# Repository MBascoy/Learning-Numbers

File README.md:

# Learning Numbers
This is a little educational game for kids (around 3-5 years old) to learn numbers and counting.

## How to play
The game has 3 modes:
- Easy Mode
- Hard Mode
- Practice Mode

In **Easy Mode** the game displays a random number between 1 and 5, you have to use the two button rows on the bottom to turn on the lights to match the number diplayed (eg: if a 3 is shown you have to press 3 buttons to turn on 3 lights), after that you press "**OK**", if the result is correct you will see a "happy face" and a new number will be shown, if the result is incorrect you will see a "sad face" and you have to correct your answer and try it again.

**Hard Mode** is the same as easy but with numbers between 6 and 16.

In **Practice Mode** the game just show how many lights are on, so you can see which number relates to how many lights are on, (eg: if you turn on 2 lights the display will show you a 2), if you press "**OK**" the game will play an audio of the number that is displayed in the screen.

## How to build
You have to do 3 things:
- Make the 3D design
- Make the PCB (And solder all the components)
- Flash a microcontroller with the code

The components list is the following:

(All the components can be found in Aliexpress)

- 2x matrix led 8x8
- 1x Atmega168pa
- 5x 74HC595 chips
- 2x 74HC165 chips
- 16x 5mm Leds
- 1x 8Mhz crystal oscillator
- 33x 1K resistors
- 16x 10K resistors
- 1x 1Ohm resistor
- 2x 22pf smd capacitors
- 1x 100nf smd capacitor
- 1x 470uf electrolitic capacitor
- 17x SMD Push buttons 12mm
- 5x SMD Push buttons 6mm
- 1x ZIF socket 28pin narrow
- 1x Power switch
- 3x JST connector ph2.0
- 1x battery holder 4x AAA
- 2x Screw M2 inserts (3mm height, 3mm OD)
- 4x M2 Screws
- 2x M2 Nuts
- 6x Screw M3 inserts (5mm height, 5mm OD)
- 4x Screw M3 inserts (3mm height, 5mm OD)
- 8x M3 Screws
- 1x DFPlayer mini
- 1x Speaker 3W 4Ohm PH2.0 terminal

For the **speaker** you need this specific model:

For the **power switch** you need this specific model:

You need to add a JST connector (PH 2.0) to the power switch and the battery holder, this is an image of the power switch with the PH 2.0 connector:

### Make the 3D design
Inside **3D design** folder you can find the 3 .stl files ready to print.

If you want to change the text (currently are on spanish), you can do it inside **global_constants.scad** file, after that you have to re-render **learning_numbers.scad** file with **openSCAD** and export the .stl file.

Once you have the 3D design printed you have to put the **screw inserts**:
- 4x M3 inserts (5mm height, 5mm OD) for the lit

- 2x M3 inserts (5mm height, 5mm OD) for battery lit

- 4x M3 inserts (3mm height, 5mm OD) for the PCB

- 2x M2 inserts (3mm height, 3mm OD) for the speaker

### Make the PCB
Inside **circuit/Learning_Numbers** folder you can find **Gerber.zip** file which has the PCB ready to be created using a your favorite provider. I've use [jlcpcb.com](https://jlcpcb.com).

When you have the PCB you need to solder the components.

Images of the PCB with no components:

Image of the final result with all the components:

### Flash code to microcontroller
The code is ready to flash with a **usbasp** programmer and an **ATMEGA168pa** microcontroller, you only have to go to the **code** folder and run `make flash` command, if you want to use other programmer or microcontroller (an ATMEGA328p for example) you have to update the **Makefile**.

**NOTE:** you have to enable the fuse to use the external crystal, use the following command (for usbasp programmer and atmega168pa microcontroller):
`avrdude -c usbasp -p m168pa -U lfuse:w:0x7F:m`

Once you have flashed the microcontroller just put it inside the ZIF socket on the PCB.

## Audio files
The game uses a **DFPlayer mini** module to play sounds, you need an micro-SD card to put inside the module, the micro-SD card must be formated with **FAT32** file system.

The files inside the micro-SD card must be the followings:

| File name  | Sound         |
| ---------- | ------------- |
| 001.mp3    | Zero          |
| 002.mp3    | One           |
| 003.mp3    | Two           |
| 004.mp3    | Three         |
| 005.mp3    | Four          |
| 006.mp3    | Five          |
| 007.mp3    | Six           |
| 008.mp3    | Seven         |
| 009.mp3    | Eight         |
| 010.mp3    | Nine          |
| 011.mp3    | Ten           |
| 012.mp3    | Eleven        |
| 013.mp3    | Twelve        |
| 014.mp3    | Thriteen      |
| 015.mp3    | Fourteen      |
| 016.mp3    | Fifteen       |
| 017.mp3    | Sixteen       |
| 018.mp3    | Title sound   |
| 019.mp3    | Easy mode     |
| 020.mp3    | Hard mode     |
| 021.mp3    | Practice mode |
| 022.mp3    | Success sound |
| 023.mp3    | Fail sound    |
| 024.mp3    | Volume Up     |
| 025.mp3    | Volume Down   |

You can find sample sounds inside the **audio samples** folder.

If you want to add your custom audios the mp3 files should have this parameters (it's not critical, but better for a good performance):

| Parameters | Value     |
| ---------- | --------- |
| Format     | mp3       |
| Channels   | Mono      |
| Samples    | 44100Hz   |
| Speed mode | Constant  |
| Quality    | 112kbps   |

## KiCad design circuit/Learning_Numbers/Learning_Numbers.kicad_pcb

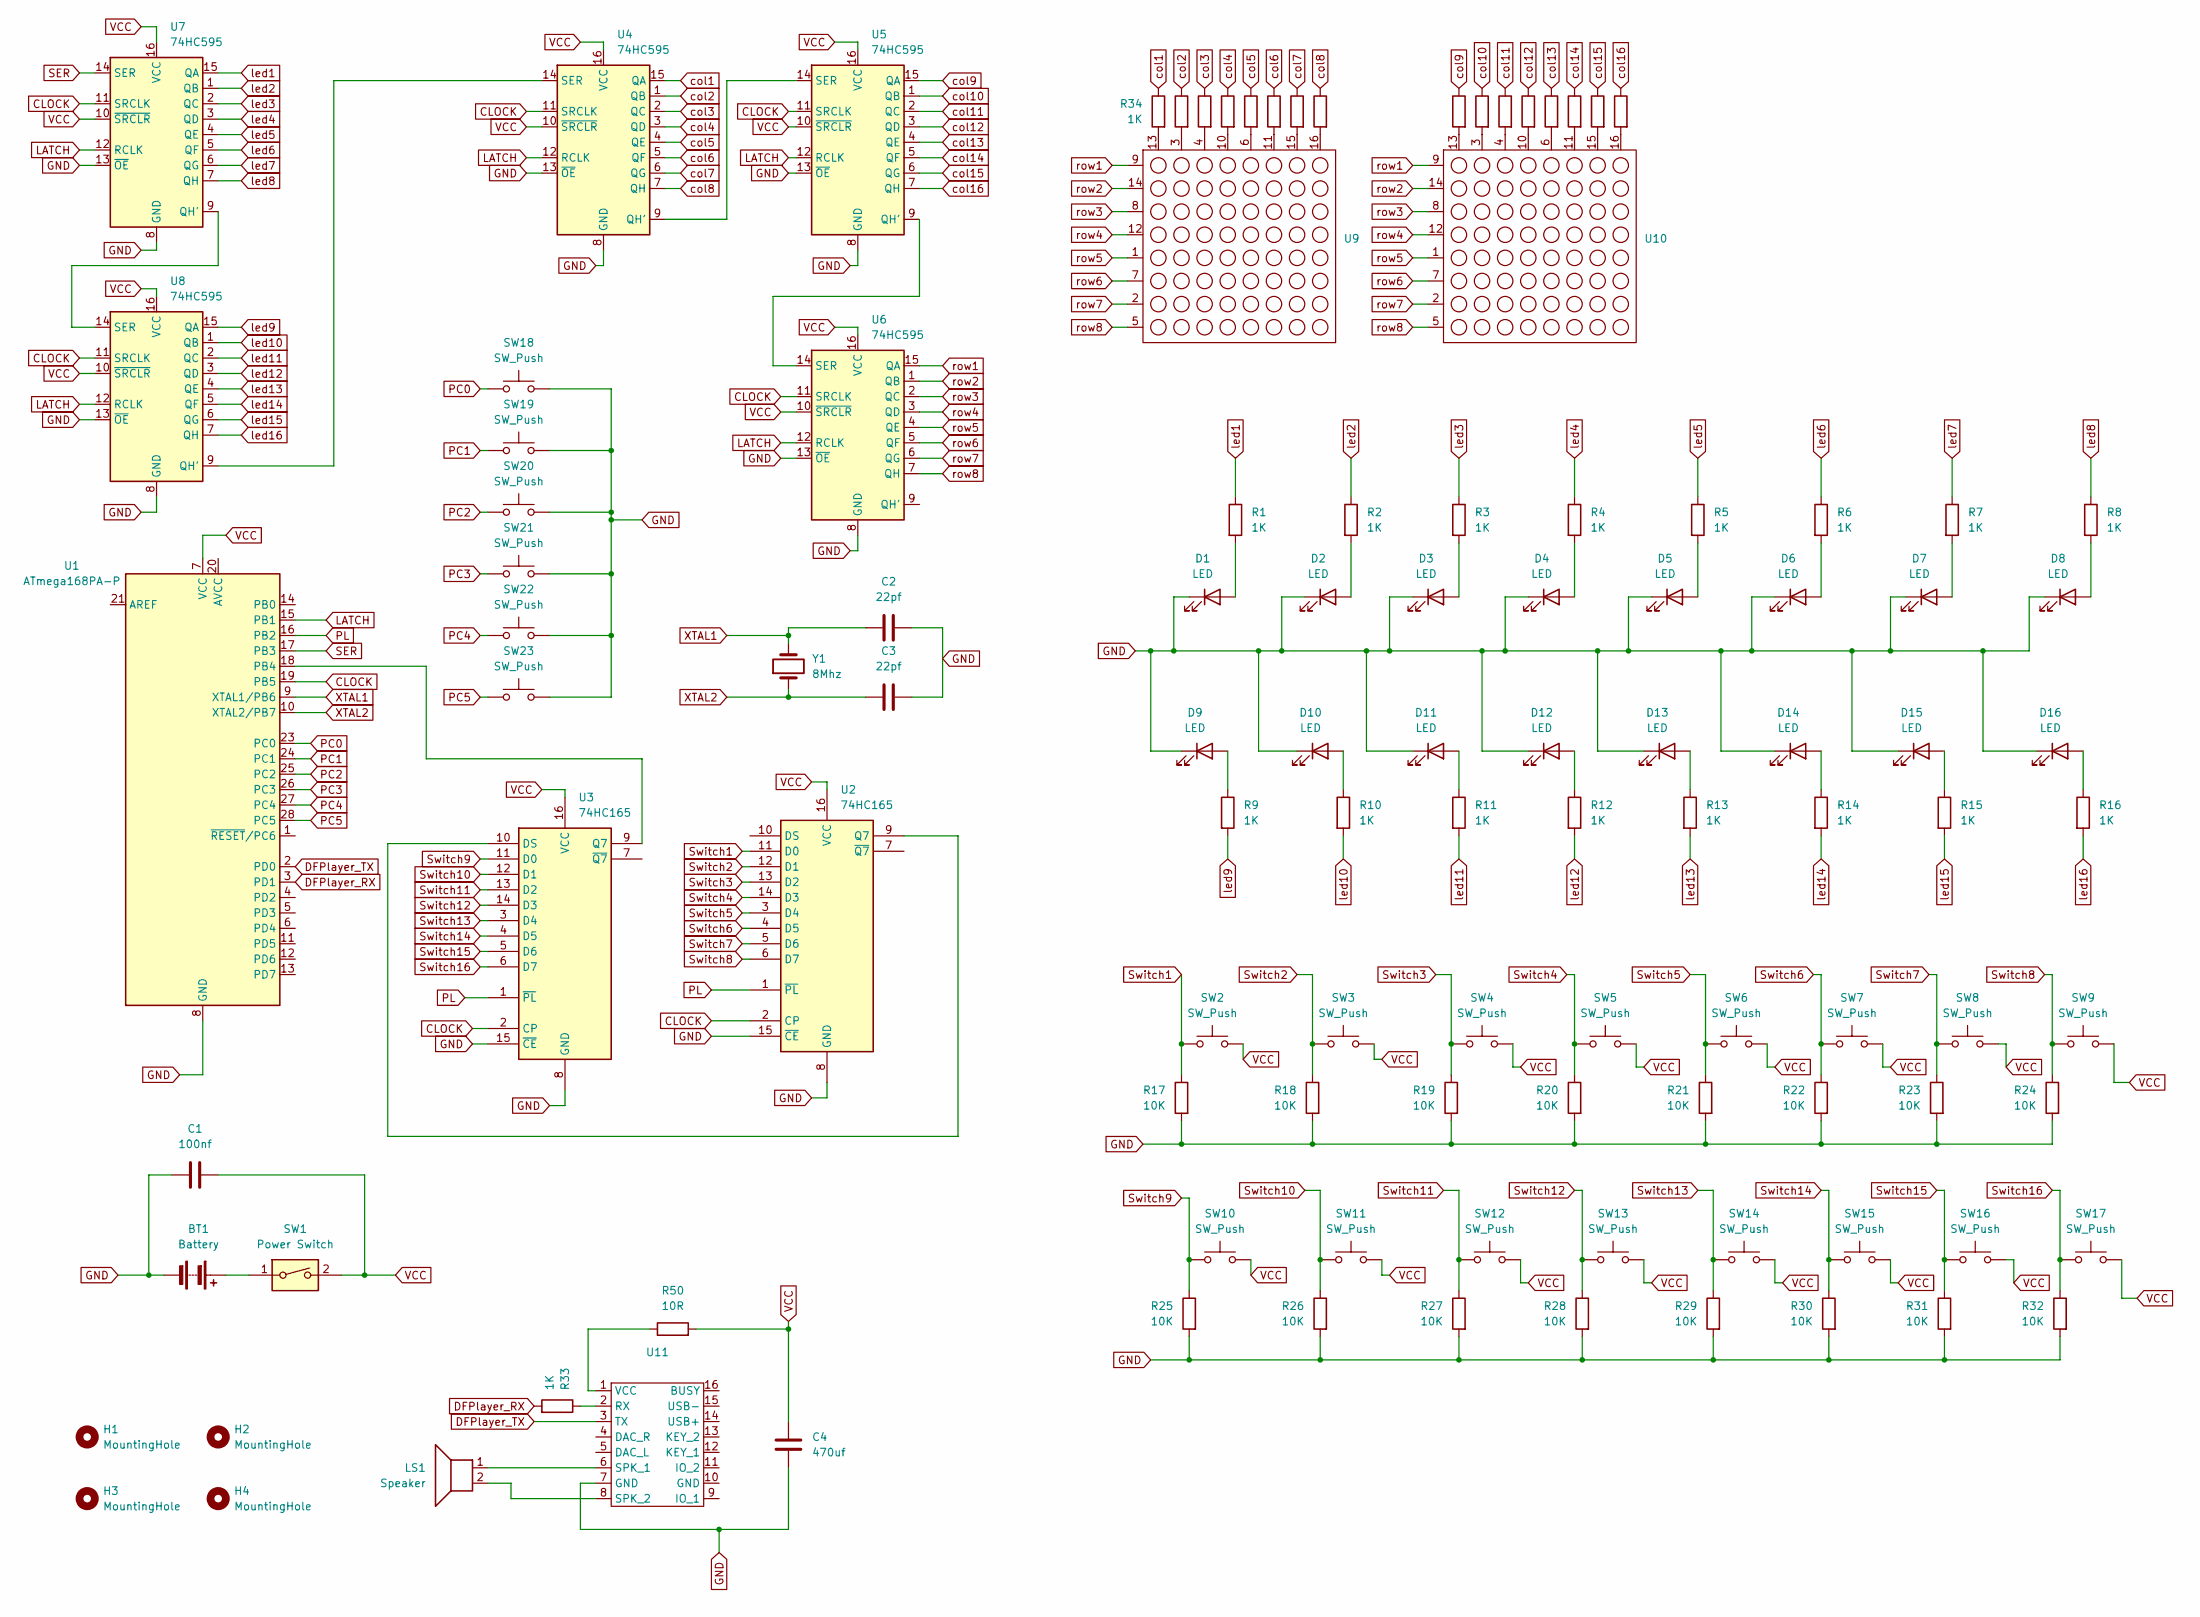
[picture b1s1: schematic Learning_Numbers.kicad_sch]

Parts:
BT1: Battery; JST_PH_S2B-PH-K_1x02_P2.00mm_Horizontal
C1: 100nf; C_1206_3216Metric_Pad1.33x1.80mm_HandSolder
C2, C3: 22pf; C_1206_3216Metric_Pad1.33x1.80mm_HandSolder
C4: 470uf; C_Elec_8x10.2
D1, D2, D3, D4, D5, D6, D7, D8, D9, D10, D11, D12, D13, D14, D15, D16: LED; LED_D5.0mm
H1, H2, H3, H4: MountingHole; MountingHole_3.2mm_M3
LS1: Speaker; JST_PH_S2B-PH-K_1x02_P2.00mm_Horizontal
R1, R2, R3, R4, R5, R6, R7, R8, R9, R10, R11, R12, R13, R14, R15, R16, R33, R34, R35, R36, R37, R38, R39, R40, R41, R42, R43, R44, R45, R46, R47, R48, R49: 1K; R_1206_3216Metric_Pad1.30x1.75mm_HandSolder
R17, R18, R19, R20, R21, R22, R23, R24, R25, R26, R27, R28, R29, R30, R31, R32: 10K; R_1206_3216Metric_Pad1.30x1.75mm_HandSolder
R50: 10R; R_1206_3216Metric_Pad1.30x1.75mm_HandSolder
SW1: Power Switch; JST_PH_S2B-PH-K_1x02_P2.00mm_Horizontal
SW2, SW3, SW4, SW5, SW6, SW7, SW8, SW9, SW10, SW11, SW12, SW13, SW14, SW15, SW16, SW17: SW_Push; SW_Push_1P1T_NO_CK_PTS125Sx73SMTR
SW18: SW_Push; SW_Push_1P1T_NO_CK_PTS125Sx43SMTR
SW19, SW20, SW21, SW22, SW23: SW_Push; SW_Push_1P1T_NO_CK_KSC7xxJ
U1: ATmega168PA-P; ZIF_Socket-28_W7.62
U2, U3: 74HC165; 74HC165D
U4, U5, U6, U7, U8: 74HC595; 74HC595D
U9, U10: 1088AS_Led_3mm_size_32mm
U11: DFPlayer_mini
Y1: 8Mhz; Crystal_HC49-4H_Vertical

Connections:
CLOCK: U1.19 (PB5), U2.2 (CP), U3.2 (CP), U4.11 (SRCLK), U5.11 (SRCLK), U6.11 (SRCLK), U7.11 (SRCLK), U8.11 (SRCLK)
DFPlayer_RX: R33.2, U1.3 (PD1)
DFPlayer_TX: U1.2 (PD0), U11.3 (TX)
GND: BT1.2 (-), C1.2, C2.2, C3.2, C4.2, D1.1 (K), D2.1 (K), D3.1 (K), D4.1 (K), D5.1 (K), D6.1 (K), D7.1 (K), D8.1 (K), D9.1 (K), D10.1 (K), D11.1 (K), D12.1 (K), D13.1 (K), D14.1 (K), D15.1 (K), D16.1 (K), R17.2, R18.2, R19.2, R20.2, R21.2, R22.2, R23.2, R24.2, R25.2, R26.2, R27.2, R28.2, R29.2, R30.2, R31.2, R32.2, SW18.2, SW19.2, SW20.2, SW21.2, SW22.2, SW23.2, U1.8 (GND), U1.22 (GND), U2.8 (GND), U2.15 (~CE), U3.8 (GND), U3.15 (~CE), U4.8 (GND), U4.13 (~OE), U5.8 (GND), U5.13 (~OE), U6.8 (GND), U6.13 (~OE), U7.8 (GND), U7.13 (~OE), U8.8 (GND), U8.13 (~OE), U11.7 (GND)
LATCH: U1.15 (PB1), U4.12 (RCLK), U5.12 (RCLK), U6.12 (RCLK), U7.12 (RCLK), U8.12 (RCLK)
unnamed: BT1.1 (+), SW1.1
unnamed: D1.2 (A), R1.2
unnamed: D2.2 (A), R2.2
unnamed: D3.2 (A), R3.2
unnamed: D4.2 (A), R4.2
unnamed: D5.2 (A), R5.2
unnamed: D6.2 (A), R6.2
unnamed: D7.2 (A), R7.2
unnamed: D8.2 (A), R8.2
unnamed: D9.2 (A), R9.1
unnamed: D10.2 (A), R10.1
unnamed: D11.2 (A), R11.1
unnamed: D12.2 (A), R12.1
unnamed: D13.2 (A), R13.1
unnamed: D14.2 (A), R14.1
unnamed: D15.2 (A), R15.1
unnamed: D16.2 (A), R16.1
unnamed: R34.2, U9.13
unnamed: R35.2, U9.3
unnamed: R36.2, U9.4
unnamed: R37.2, U9.10
unnamed: R38.2, U9.6
unnamed: R39.2, U9.11
unnamed: R40.2, U9.15
unnamed: R41.2, U9.16
unnamed: R42.2, U10.13
unnamed: R43.2, U10.3
unnamed: R44.2, U10.4
unnamed: R45.2, U10.10
unnamed: R46.2, U10.6
unnamed: R47.2, U10.11
unnamed: R48.2, U10.15
unnamed: R49.2, U10.16
unnamed: U1.18 (PB4), U3.9 (Q7)
unnamed: U2.9 (Q7), U3.10 (DS)
unnamed: U4.9 (QH'), U5.14 (SER)
unnamed: U4.14 (SER), U8.9 (QH')
unnamed: U5.9 (QH'), U6.14 (SER)
unnamed: U7.9 (QH'), U8.14 (SER)
unnamed: R33.1, U11.2 (RX)
unnamed: LS1.1, U11.6 (SPK_1)
unnamed: LS1.2, U11.8 (SPK_2)
unnamed: R50.1, U11.1 (VCC)
PC0: SW18.1, U1.23 (PC0)
PC1: SW19.1, U1.24 (PC1)
PC2: SW20.1, U1.25 (PC2)
PC3: SW21.1, U1.26 (PC3)
PC4: SW22.1, U1.27 (PC4)
PC5: SW23.1, U1.28 (PC5)
PL: U1.16 (PB2), U2.1 (~PL), U3.1 (~PL)
SER: U1.17 (PB3), U7.14 (SER)
Switch1: R17.1, SW2.1, U2.11 (D0)
Switch2: R18.1, SW3.1, U2.12 (D1)
Switch3: R19.1, SW4.1, U2.13 (D2)
Switch4: R20.1, SW5.1, U2.14 (D3)
Switch5: R21.1, SW6.1, U2.3 (D4)
Switch6: R22.1, SW7.1, U2.4 (D5)
Switch7: R23.1, SW8.1, U2.5 (D6)
Switch8: R24.1, SW9.1, U2.6 (D7)
Switch9: R25.1, SW10.1, U3.11 (D0)
Switch10: R26.1, SW11.1, U3.12 (D1)
Switch11: R27.1, SW12.1, U3.13 (D2)
Switch12: R28.1, SW13.1, U3.14 (D3)
Switch13: R29.1, SW14.1, U3.3 (D4)
Switch14: R30.1, SW15.1, U3.4 (D5)
Switch15: R31.1, SW16.1, U3.5 (D6)
Switch16: R32.1, SW17.1, U3.6 (D7)
VCC: C1.1, C4.1, R50.2, SW1.2, SW2.2, SW3.2, SW4.2, SW5.2, SW6.2, SW7.2, SW8.2, SW9.2, SW10.2, SW11.2, SW12.2, SW13.2, SW14.2, SW15.2, SW16.2, SW17.2, U1.7 (VCC), U2.16 (VCC), U3.16 (VCC), U4.10 (~SRCLR), U4.16 (VCC), U5.10 (~SRCLR), U5.16 (VCC), U6.10 (~SRCLR), U6.16 (VCC), U7.10 (~SRCLR), U7.16 (VCC), U8.10 (~SRCLR), U8.16 (VCC)
XTAL1: C2.1, U1.9 (XTAL1/PB6), Y1.2
XTAL2: C3.1, U1.10 (XTAL2/PB7), Y1.1
col1: R34.1, U4.15 (QA)
col2: R35.1, U4.1 (QB)
col3: R36.1, U4.2 (QC)
col4: R37.1, U4.3 (QD)
col5: R38.1, U4.4 (QE)
col6: R39.1, U4.5 (QF)
col7: R40.1, U4.6 (QG)
col8: R41.1, U4.7 (QH)
col9: R42.1, U5.15 (QA)
col10: R43.1, U5.1 (QB)
col11: R44.1, U5.2 (QC)
col12: R45.1, U5.3 (QD)
col13: R46.1, U5.4 (QE)
col14: R47.1, U5.5 (QF)
col15: R48.1, U5.6 (QG)
col16: R49.1, U5.7 (QH)
led1: R1.1, U7.15 (QA)
led2: R2.1, U7.1 (QB)
led3: R3.1, U7.2 (QC)
led4: R4.1, U7.3 (QD)
led5: R5.1, U7.4 (QE)
led6: R6.1, U7.5 (QF)
led7: R7.1, U7.6 (QG)
led8: R8.1, U7.7 (QH)
led9: R9.2, U8.15 (QA)
led10: R10.2, U8.1 (QB)
led11: R11.2, U8.2 (QC)
led12: R12.2, U8.3 (QD)
led13: R13.2, U8.4 (QE)
led14: R14.2, U8.5 (QF)
led15: R15.2, U8.6 (QG)
led16: R16.2, U8.7 (QH)
row1: U6.15 (QA), U9.9, U10.9
row2: U6.1 (QB), U9.14, U10.14
row3: U6.2 (QC), U9.8, U10.8
row4: U6.3 (QD), U9.12, U10.12
row5: U6.4 (QE), U9.1, U10.1
row6: U6.5 (QF), U9.7, U10.7
row7: U6.6 (QG), U9.2, U10.2
row8: U6.7 (QH), U9.5, U10.5

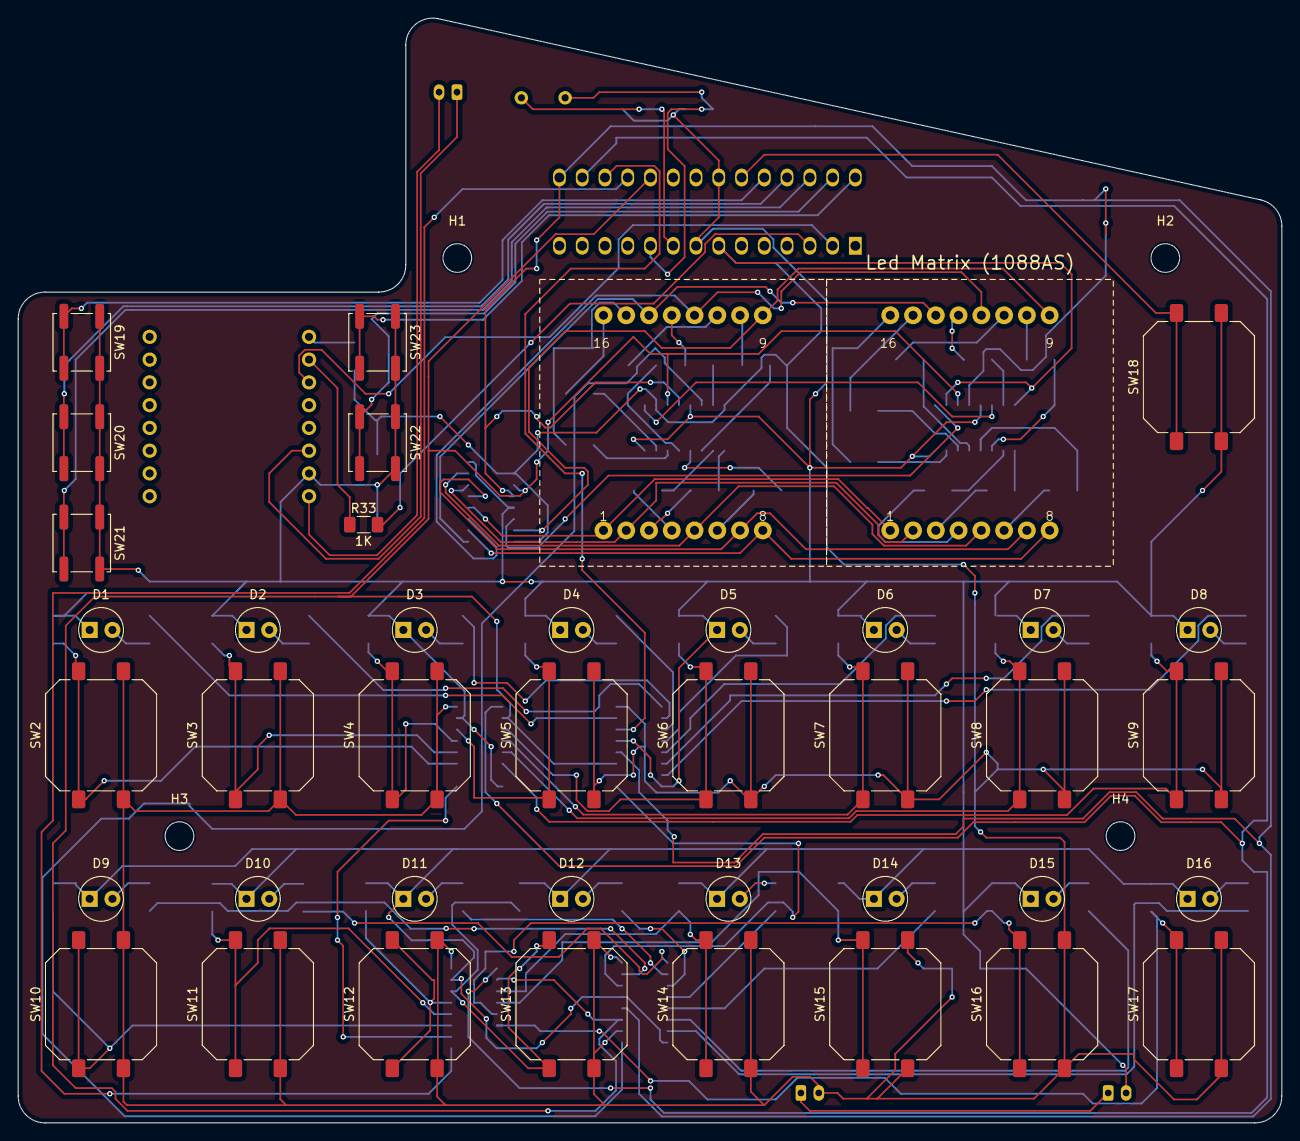
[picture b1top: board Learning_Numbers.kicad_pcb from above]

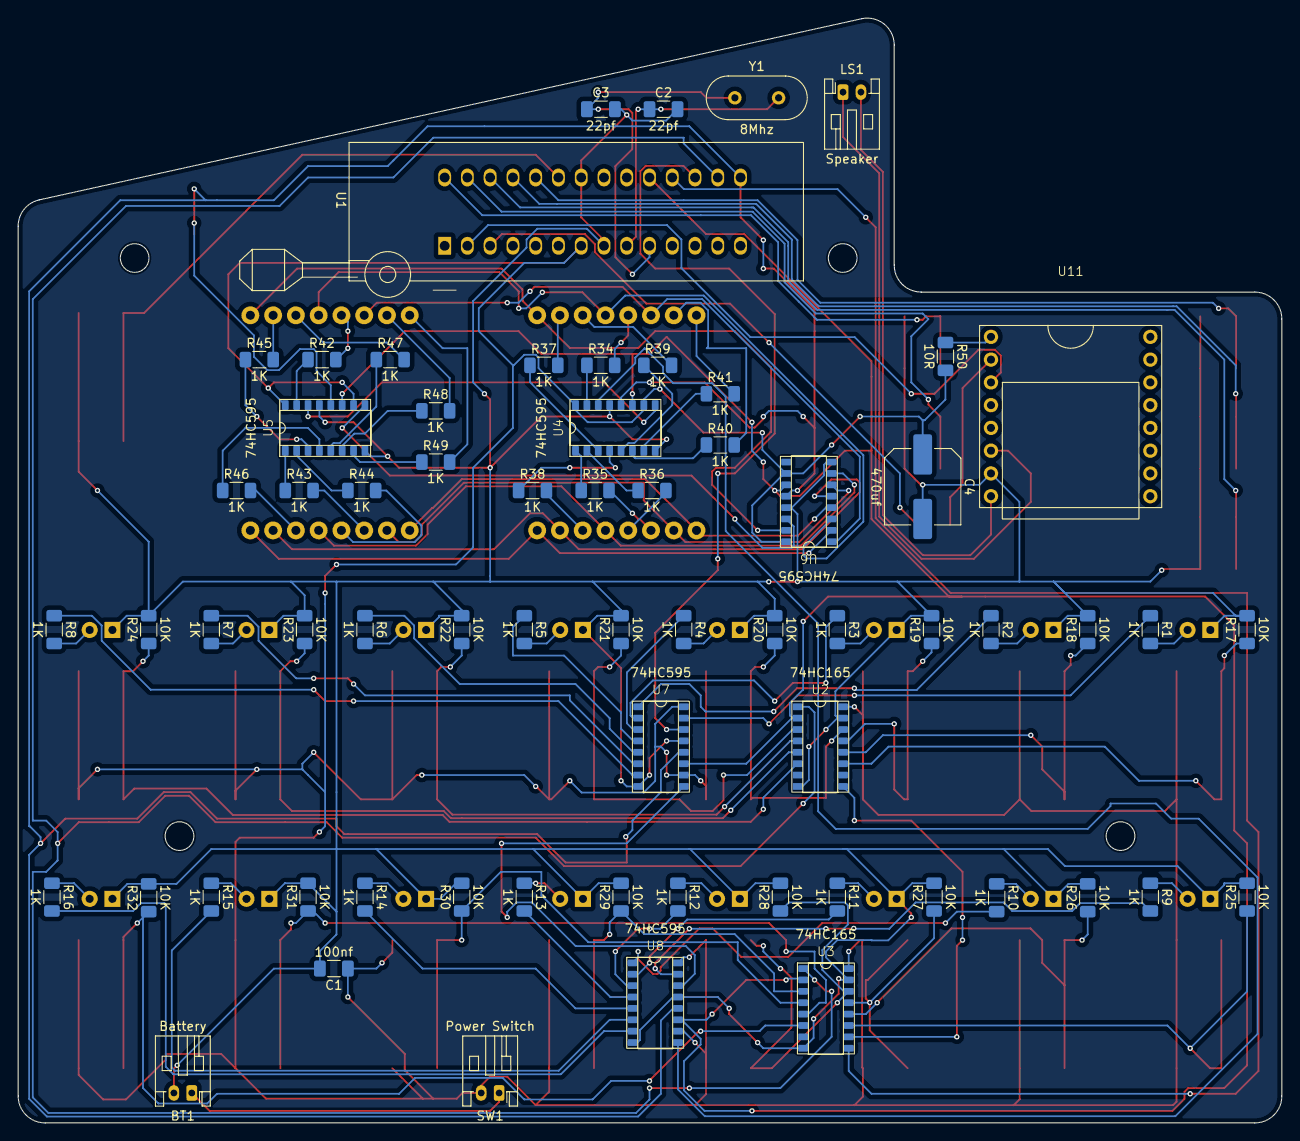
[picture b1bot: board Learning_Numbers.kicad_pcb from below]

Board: 2 copper layers, 141.0 x 123.3 mm, 111 parts (66 on the bottom side), 115 nets.

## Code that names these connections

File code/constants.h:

// Definiciones de pines
#define DDR_SPI  DDRB
#define DD_MISO  PB4
#define DD_SCK   PB5
#define DD_MOSI    PB3 // El pin SS debe ser salida para modo Master
#define PL_PIN   PB2  // Pin para Parallel Load
#define LATCH_PIN   PB1  // Pin para Parallel Load

#define ANIMATION_DELAY 90 // Miliseconds for animation steps
#define ANIMATION_DURATION 1000 // How much Animation lasts
#define DEBOUNCE_DURATION 170 // iterations for button debounce
#define RESULT_DURATION 1500 // Miliseconds to show result before next level

#define START_AUDIO 18 // Track to play when starting a game
#define EASY_MODE_AUDIO 19
#define HARD_MODE_AUDIO 20
#define PRACTICE_MODE_AUDIO 21
#define SUCCESS_AUDIO 22 // Track to play on success
#define FAILURE_AUDIO 23 // Track to play on failure
#define VOLUME_UP_AUDIO 24 // Track to play on failure
#define VOLUME_DOWN_AUDIO 25 // Track to play on failure

#define DEFAULT_VOLUME 15 // Default volume level (0-30)

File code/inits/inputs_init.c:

#include <avr/io.h>

void inputs_init(){
    //set PC0, PC1, PC2, PC3 as inputs
    DDRC &= ~((1 << PC0) | (1 << PC1) | (1 << PC2) | (1 << PC3)) | (1 << PC4) | (1 << PC5);

    // TEMPORAL !!!!!!!!!!!!
    DDRD = 0b00000011;

    //pull-up resistors
    PORTC |= (1 << PC0) | (1 << PC1) | (1 << PC2) | (1 << PC3) | (1 << PC4) | (1 << PC5);

    PCICR |= (1 << PCIE1);
    PCMSK1 |= (1 << PC0) | (1 << PC1) | (1 << PC2) | (1 << PC3) | (1 << PC4) | (1 << PC5);
}

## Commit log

2025-12-18 Add 3d design
2025-12-19 add pcb anchors and power switch hole
2025-12-19 update variables
2025-12-25 add simulation and basic code
2025-12-25 put numbers as a global variable
2025-12-25 code refactor and add basic modes
2025-12-26 add animations
2025-12-27 complete game logic, new animations and some refactors
2025-12-30 add debounce for inputs
2026-01-04 add audio code
2026-01-04 update 3D design
2026-01-06 update 3D design parameters
2026-01-06 add Kicad circuit
2026-01-07 finish circuit pathing
2026-01-07 add crystal to circuit
2026-01-08 add battery case to 3d design
2026-01-09 update battery box
2026-01-09 add battery screws
2026-01-09 add battery anchors
2026-01-09 3D design finish battery cover
2026-01-10 add body text
2026-01-12 update pcb silk layer
2026-01-24 update 3D design and circuit
2026-01-24 update code, switch inputs, boot sequence and sounds
2026-01-26 add final adjust to 3d design and code
2026-02-01 update practice mode to start in 1
2026-02-02 add README.md and audio samples
2026-02-02 Add new images to README, update 3d design text variables
2026-02-16 rescale images
2026-02-16 update circuit add capacitor DFPlayer and change speaker conections
2026-02-16 update code change constants
2026-02-21 add test leds and adjust audio volume
2026-02-23 update README to add images
2026-02-23 Update README component list
2026-02-23 Update circuit to add DFPlayer 10 ohm resistor
2026-02-23 Update code to change max volume and add initial test for leds
2026-02-23 Update README to add component description
2026-03-17 Update gerber files
